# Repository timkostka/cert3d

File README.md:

# cert3d

Is your 3d printer firmware certified?

# What is Cert3D?

Cert3D is a project designed to certify the performance of 3d printer firmware.  It works by sending test g-code to the printer and monitoring the output of stepper motors.

## Why is Cert3D?

Within the 3d printer firmware community, there is a lack of verification of software features.  A massive amount of man-hours is spent on tracking down bugs which could otherwise be detected automatically.  The aim of this project is to enable developers to ensure features are working as intended before releasing software.

## Who benefits?

For developers, the testing framework helps identify bugs quickly allowing them to be fixed quickly.  The improved software quality due to this benefits.

## How does it work?

There are two parts to Cert3D--A hardware module and a software program.

### The hardware module

The hardware module is hooked up to the 3d printer board and monitors status of the stepper motors and other peripherals.

### The software program

The software sends runs a series of tests by sending g-code to the 3d printer board.  During these tests, it also reads back information from the hardware module.  It analyses these results to ensure the printer is working as intended.

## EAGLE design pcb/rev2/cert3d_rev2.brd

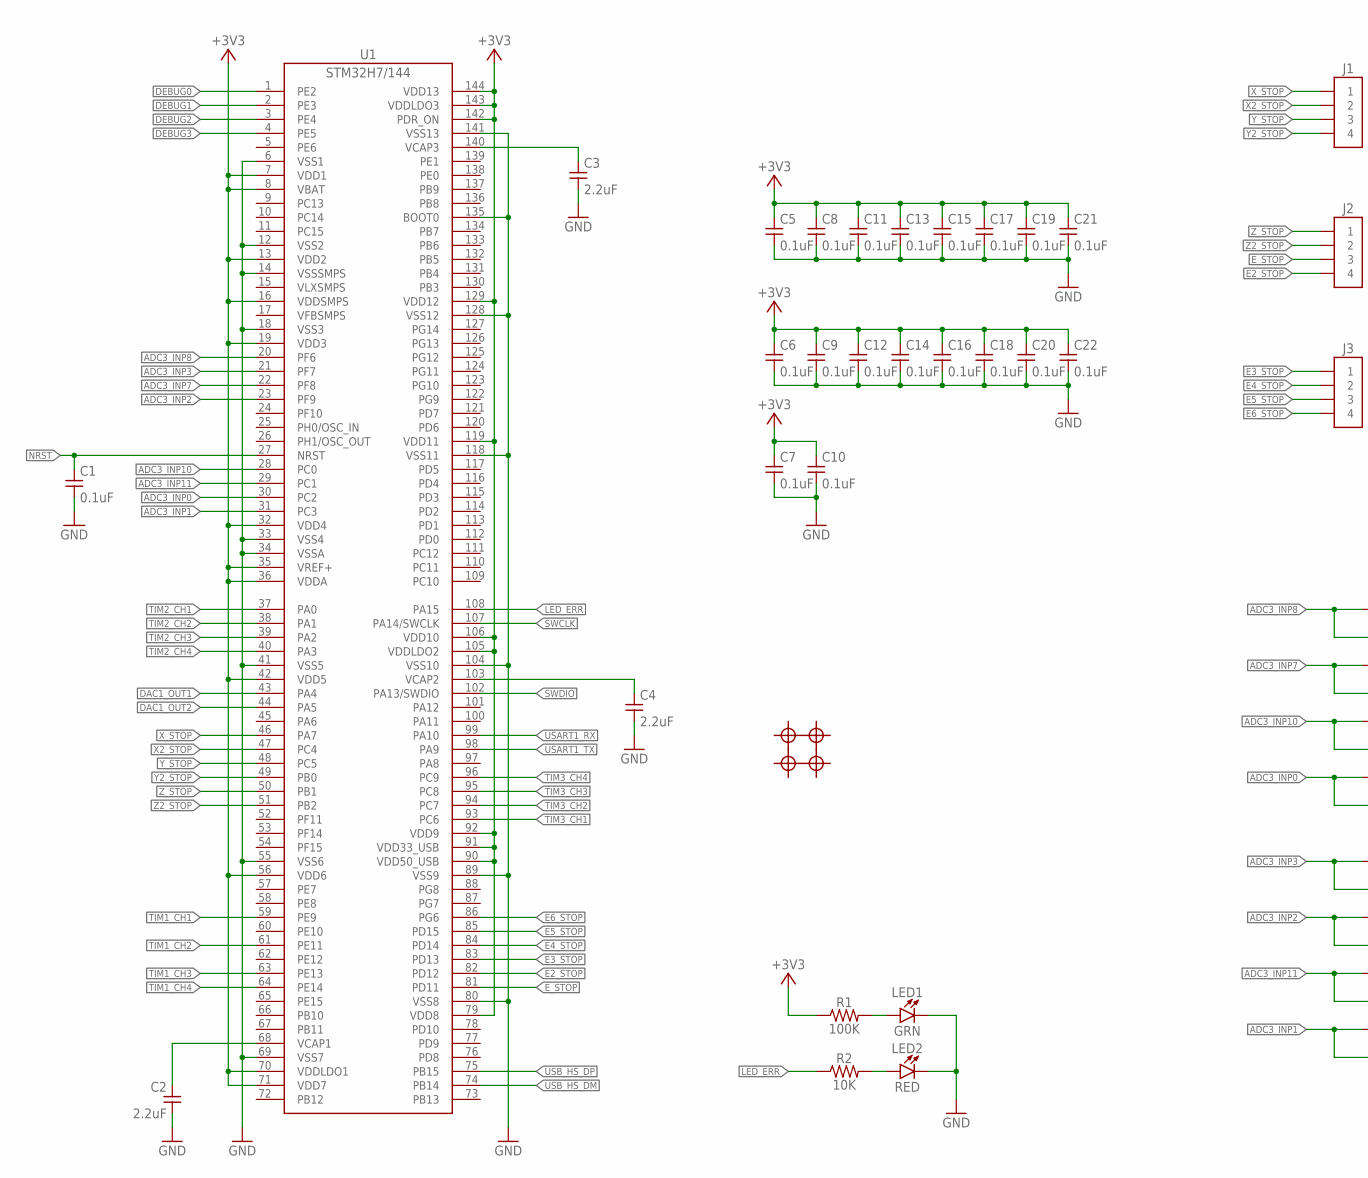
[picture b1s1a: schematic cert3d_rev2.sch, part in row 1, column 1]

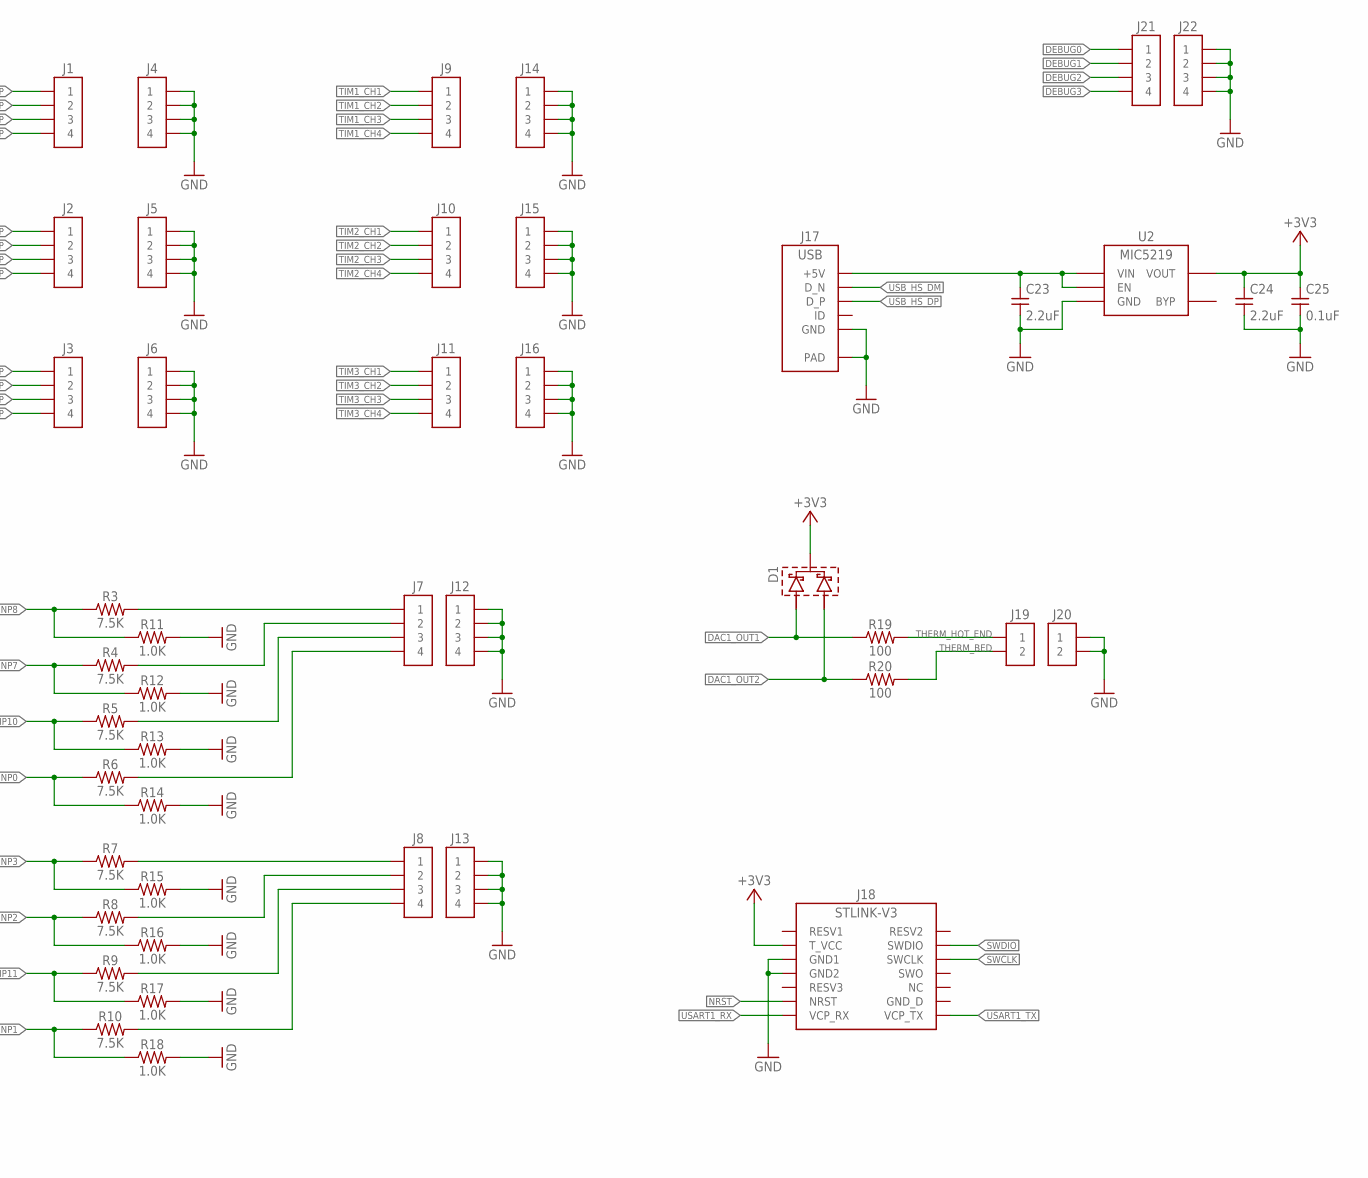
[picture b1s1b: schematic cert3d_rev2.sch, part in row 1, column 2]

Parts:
C1, C5, C6, C7, C8, C9, C10, C11, C12, C13, C14, C15, C16, C17, C18, C19, C20, C21, C22, C25: 0.1uF; C0805-5MIL
C2, C3, C4, C23, C24: 2.2uF; C0805-5MIL
D1: SCHOTTKY_DUAL_CCBAT54C; SOT23-3
FD1, FD2, FD3, FD4: FIDUCIAL; FID1MM
J1, J2, J3, J4, J5, J6, J7, J8, J9, J10, J11, J12, J13, J14, J15, J16, J21, J22: CONN4TSW-S; SAM-TSW-104-XX-X-S
J17: USB-5PINTOPVIA; HIR-ZX62R-B-5P-VIAS
J18: STLINK-V3/SWDCNC-3220; CNC-3220-14-0100-00
J19, J20: CONN2TSW-S; SAM-TSW-102-XX-X-S
LED1: GRN; CHIPLED0805-SMALL
LED2: RED; CHIPLED0805-SMALL
R1: 100K; RES0805R-5MIL
R2: 10K; RES0805R-5MIL
R3, R4, R5, R6, R7, R8, R9, R10: 7.5K; RES0805R-5MIL
R11, R12, R13, R14, R15, R16, R17, R18: 1.0K; RES0805R-5MIL
R19, R20: 100; RES0805R-5MIL
U1: STM32H745-144; LQFP144-20X20MM
U2: MIC5219; SOT23-5

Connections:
+3V3: C5.1, C6.1, C7.1, C8.1, C9.1, C10.1, C11.1, C12.1, C13.1, C14.1, C15.1, C16.1, C17.1, C18.1, C19.1, C20.1, C21.1, C22.1, C24.1, C25.1, D1.3 (C), J18.3 (T_VCC), R1.1, U1.7 (VDD1), U1.8 (VBAT), U1.13 (VDD2), U1.16 (VDDSMPS), U1.19 (VDD3), U1.32 (VDD4), U1.35 (VREF+), U1.36 (VDDA), U1.42 (VDD5), U1.56 (VDD6), U1.70 (VDDLDO1), U1.71 (VDD7), U1.79 (VDD8), U1.90 (VDD50_USB), U1.91 (VDD33_USB), U1.92 (VDD9), U1.105 (VDDLDO2), U1.106 (VDD10), U1.119 (VDD11), U1.129 (VDD12), U1.142 (PDR_ON), U1.143 (VDDLDO3), U1.144 (VDD13), U2.5 (VOUT)
ADC3_INP0: R6.1, R14.1, U1.30 (PC2)
ADC3_INP1: R10.1, R18.1, U1.31 (PC3)
ADC3_INP2: R8.1, R16.1, U1.23 (PF9)
ADC3_INP3: R7.1, R15.1, U1.21 (PF7)
ADC3_INP7: R4.1, R12.1, U1.22 (PF8)
ADC3_INP8: R3.1, R11.1, U1.20 (PF6)
ADC3_INP10: R5.1, R13.1, U1.28 (PC0)
ADC3_INP11: R9.1, R17.1, U1.29 (PC1)
DAC1_OUT1: D1.1 (A1), R19.1, U1.43 (PA4)
DAC1_OUT2: D1.2 (A2), R20.1, U1.44 (PA5)
DEBUG0: J21.1, U1.1 (PE2)
DEBUG1: J21.2, U1.2 (PE3)
DEBUG2: J21.3, U1.3 (PE4)
DEBUG3: J21.4, U1.4 (PE5)
E2_STOP: J2.4, U1.82 (PD12)
E3_STOP: J3.1, U1.83 (PD13)
E4_STOP: J3.2, U1.84 (PD14)
E5_STOP: J3.3, U1.85 (PD15)
E6_STOP: J3.4, U1.86 (PG6)
E_STOP: J2.3, U1.81 (PD11)
GND: C1.2, C2.2, C3.2, C4.2, C5.2, C6.2, C7.2, C8.2, C9.2, C10.2, C11.2, C12.2, C13.2, C14.2, C15.2, C16.2, C17.2, C18.2, C19.2, C20.2, C21.2, C22.2, C23.2, C24.2, C25.2, J4.1, J4.2, J4.3, J4.4, J5.1, J5.2, J5.3, J5.4, J6.1, J6.2, J6.3, J6.4, J12.1, J12.2, J12.3, J12.4, J13.1, J13.2, J13.3, J13.4, J14.1, J14.2, J14.3, J14.4, J15.1, J15.2, J15.3, J15.4, J16.1, J16.2, J16.3, J16.4, J17.5 (GND), J17.PAD@1 (PAD), J17.PAD@2 (PAD), J17.PAD@3 (PAD), J17.PAD@4 (PAD), J17.PAD@5 (PAD), J17.PAD@6 (PAD), J17.PAD@7 (PAD), J17.PAD@8 (PAD), J17.PAD@9 (PAD), J17.PAD@10 (PAD), J17.PAD@11 (PAD), J17.PAD@12 (PAD), J18.5 (GND1), J18.7 (GND2), J20.1, J20.2, J22.1, J22.2, J22.3, J22.4, LED1.C, LED2.C, R11.2, R12.2, R13.2, R14.2, R15.2, R16.2, R17.2, R18.2, U1.6 (VSS1), U1.12 (VSS2), U1.14 (VSSSMPS), U1.18 (VSS3), U1.33 (VSS4), U1.34 (VSSA), U1.41 (VSS5), U1.55 (VSS6), U1.69 (VSS7), U1.80 (VSS8), U1.89 (VSS9), U1.104 (VSS10), U1.118 (VSS11), U1.128 (VSS12), U1.135 (BOOT0), U1.141 (VSS13), U2.2 (GND)
LED_ERR: R2.1, U1.108 (PA15)
unnamed: C2.1, U1.68 (VCAP1)
unnamed: C4.1, U1.103 (VCAP2)
unnamed: J7.3, R5.2
unnamed: J7.1, R3.2
unnamed: J8.2, R8.2
unnamed: J7.2, R4.2
unnamed: C3.1, U1.140 (VCAP3)
unnamed: C23.1, J17.1 (+5V), U2.1 (VIN), U2.3 (EN)
unnamed: J8.3, R9.2
unnamed: J7.4, R6.2
unnamed: J8.4, R10.2
unnamed: J8.1, R7.2
unnamed: LED2.A, R2.2
unnamed: LED1.A, R1.2
NRST: C1.1, J18.11 (NRST), U1.27 (NRST)
SWCLK: J18.6 (SWCLK), U1.107 (PA14/SWCLK)
SWDIO: J18.4 (SWDIO), U1.102 (PA13/SWDIO)
THERM_BED: J19.2, R20.2
THERM_HOT_END: J19.1, R19.2
TIM1_CH1: J9.1, U1.59 (PE9)
TIM1_CH2: J9.2, U1.61 (PE11)
TIM1_CH3: J9.3, U1.63 (PE13)
TIM1_CH4: J9.4, U1.64 (PE14)
TIM2_CH1: J10.1, U1.37 (PA0)
TIM2_CH2: J10.2, U1.38 (PA1)
TIM2_CH3: J10.3, U1.39 (PA2)
TIM2_CH4: J10.4, U1.40 (PA3)
TIM3_CH1: J11.1, U1.93 (PC6)
TIM3_CH2: J11.2, U1.94 (PC7)
TIM3_CH3: J11.3, U1.95 (PC8)
TIM3_CH4: J11.4, U1.96 (PC9)
USART1_RX: J18.13 (VCP_RX), U1.99 (PA10)
USART1_TX: J18.14 (VCP_TX), U1.98 (PA9)
USB_HS_DM: J17.2 (D_N), U1.74 (PB14)
USB_HS_DP: J17.3 (D_P), U1.75 (PB15)
X2_STOP: J1.2, U1.47 (PC4)
X_STOP: J1.1, U1.46 (PA7)
Y2_STOP: J1.4, U1.49 (PB0)
Y_STOP: J1.3, U1.48 (PC5)
Z2_STOP: J2.2, U1.51 (PB2)
Z_STOP: J2.1, U1.50 (PB1)

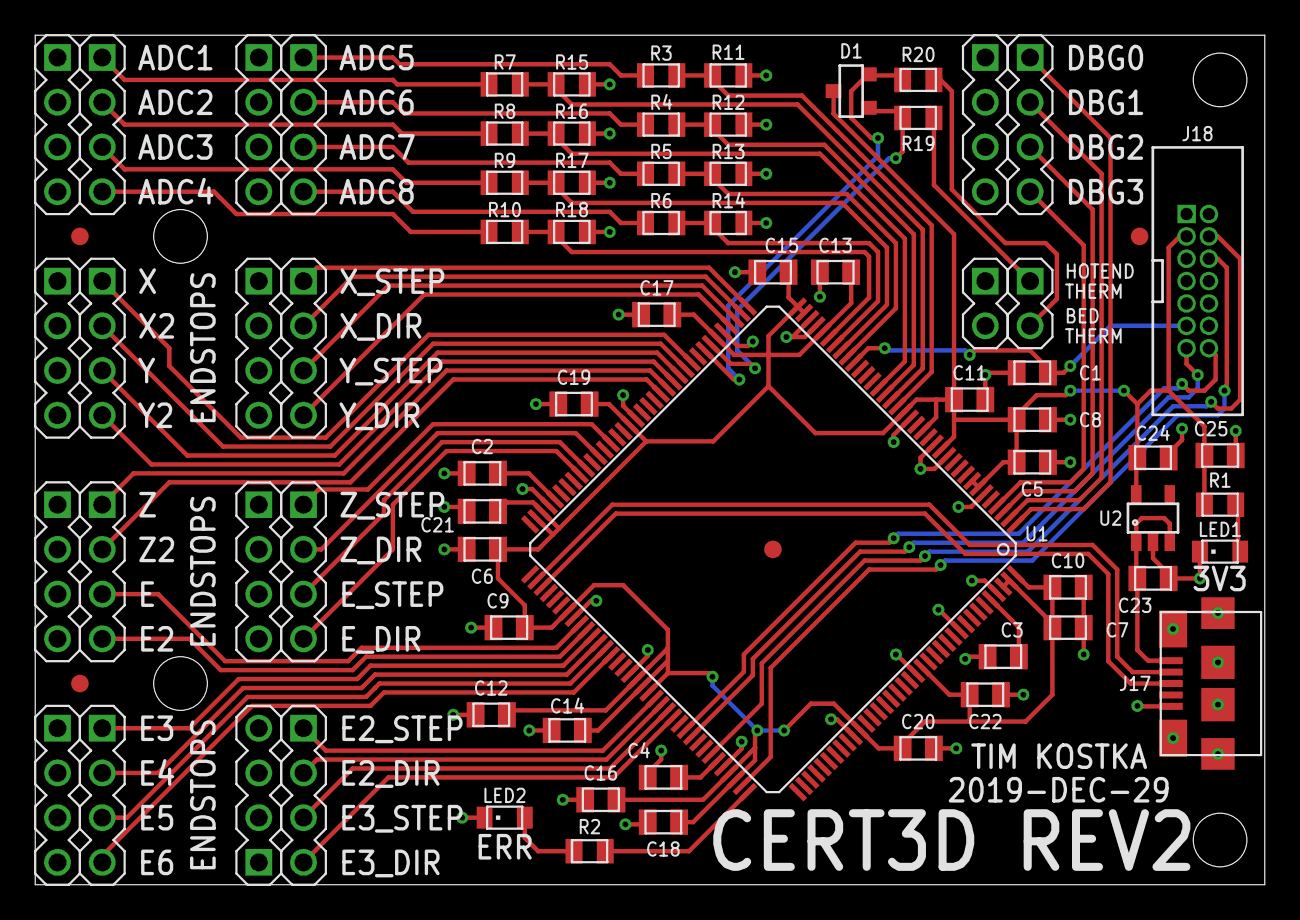
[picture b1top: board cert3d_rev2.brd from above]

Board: 2 copper layers, 69.8 x 48.3 mm, 76 parts (0 on the bottom side), 64 nets.

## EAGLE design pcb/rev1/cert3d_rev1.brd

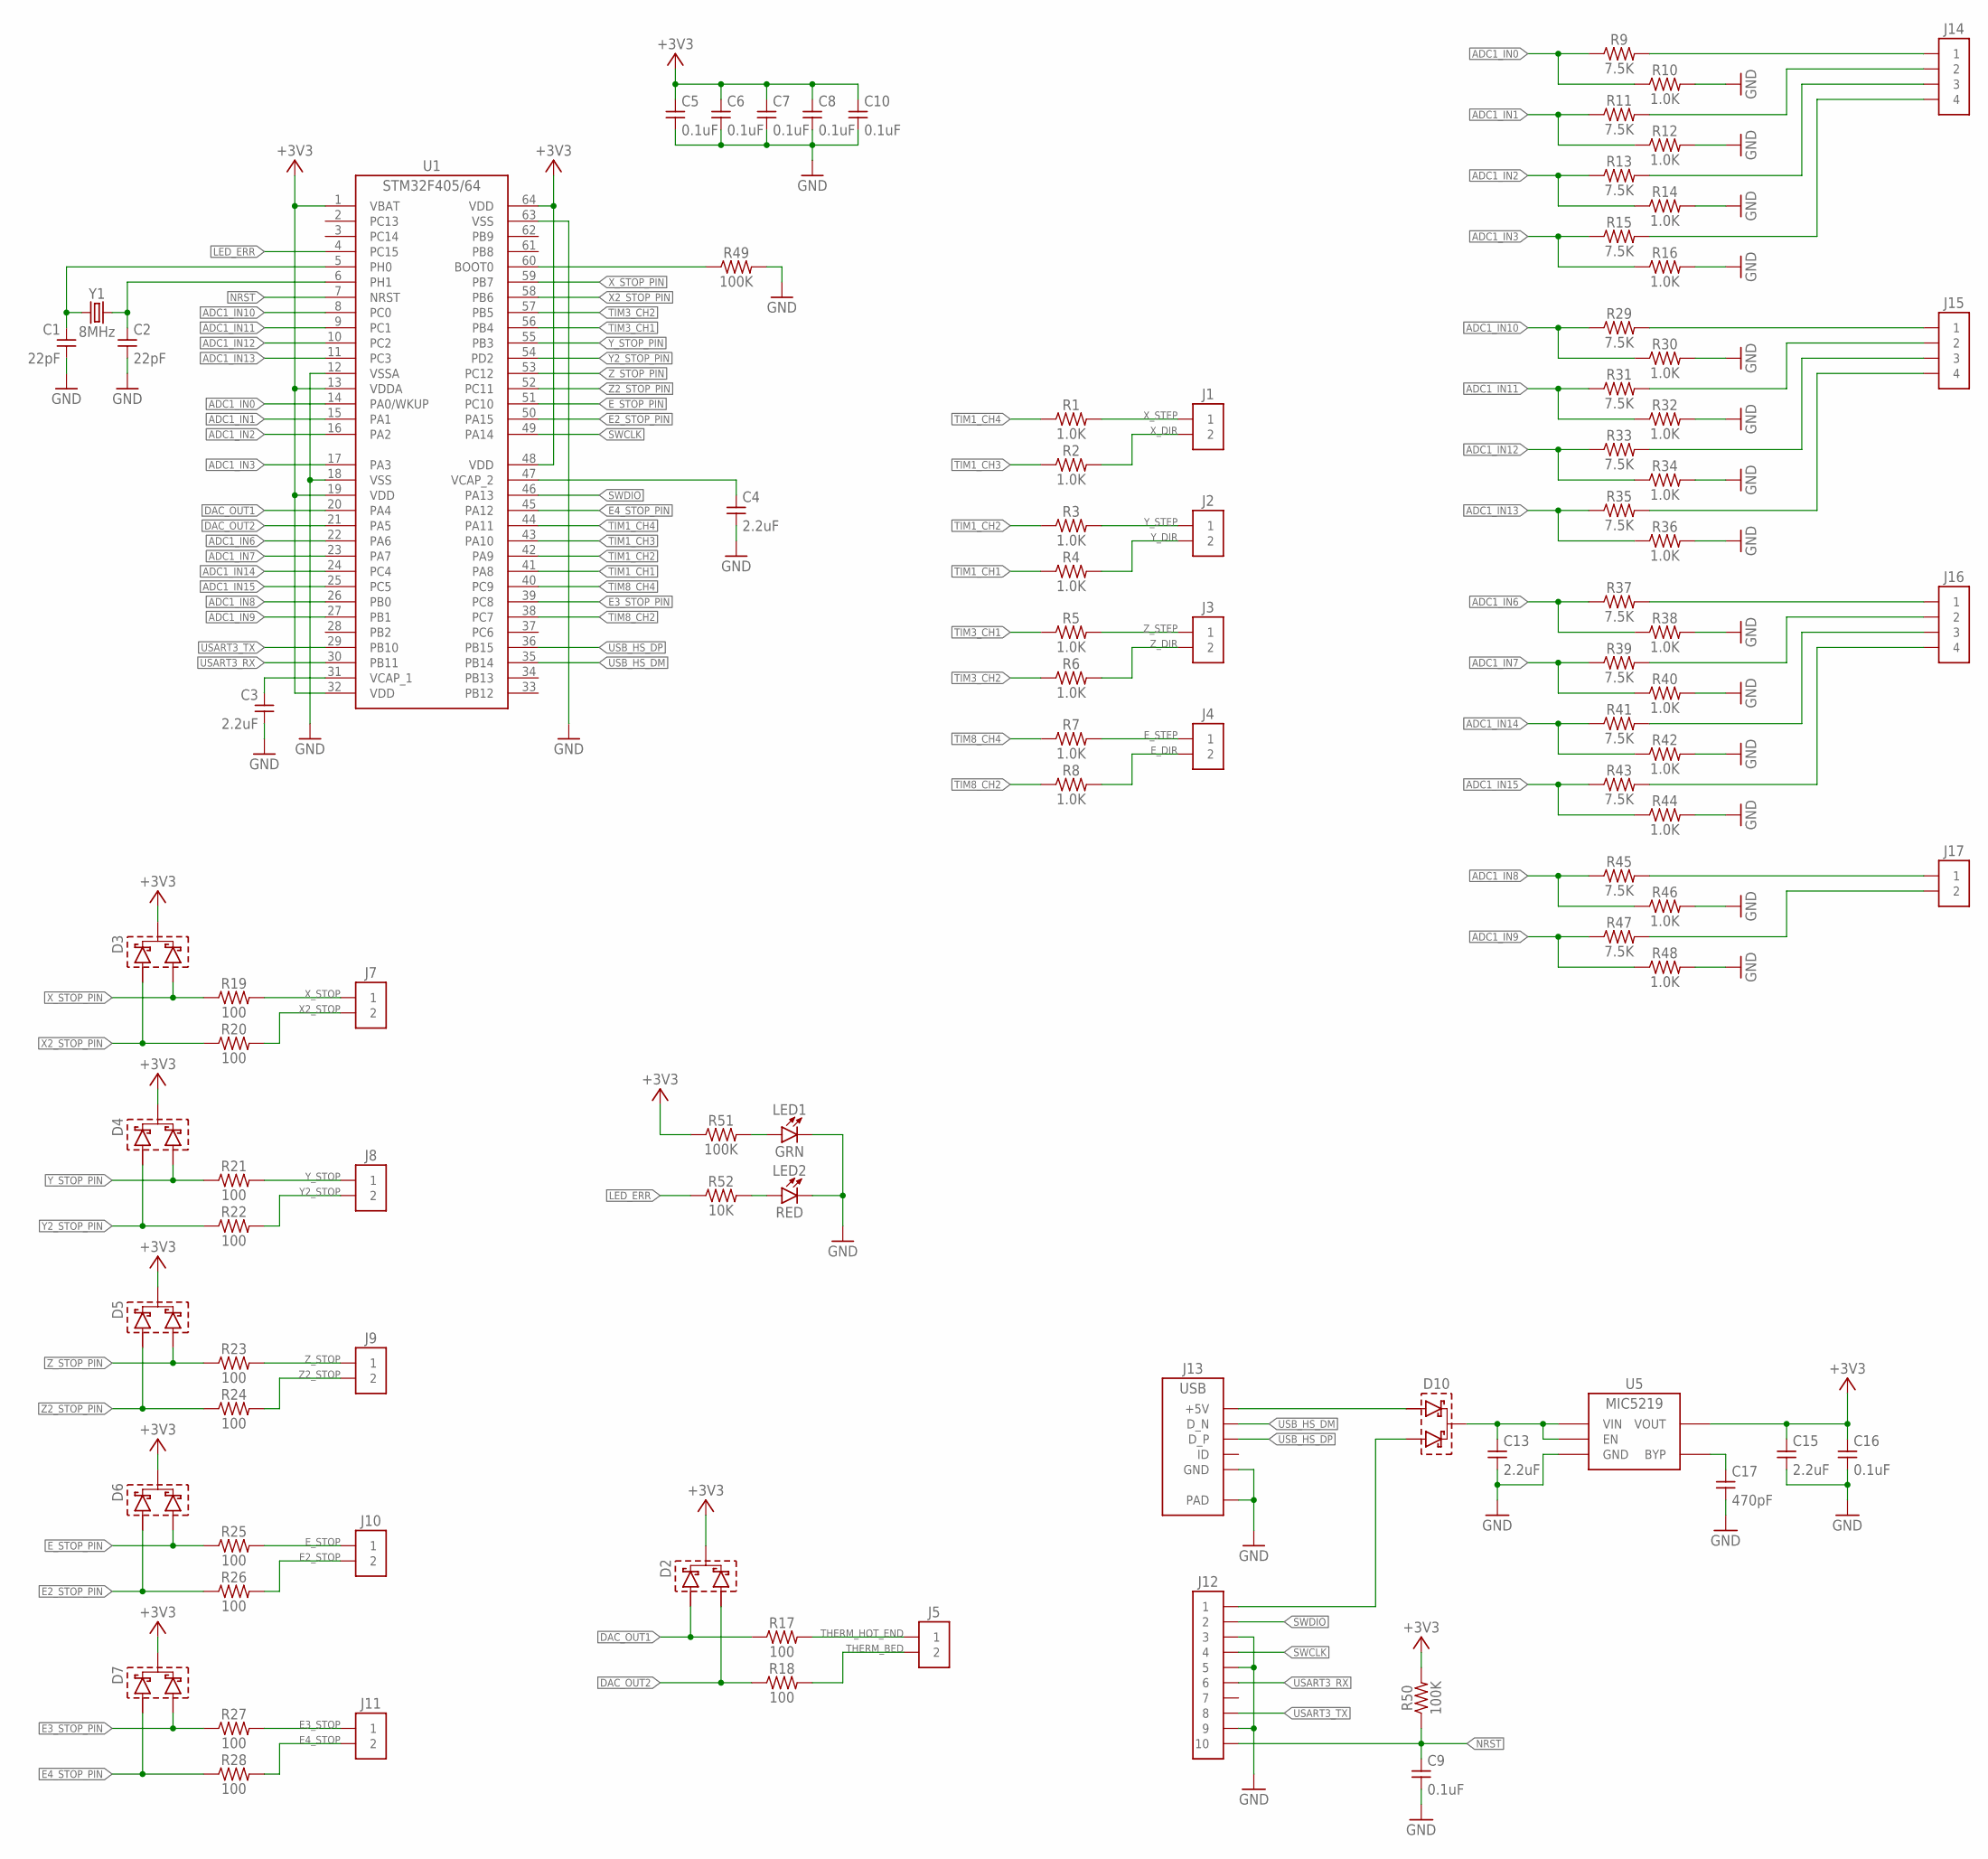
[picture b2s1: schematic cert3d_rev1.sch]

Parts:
C1, C2: 22pF; C0805-5MIL
C3, C4, C13, C15: 2.2uF; C0805-5MIL
C5, C6, C7, C8, C9, C10, C16: 0.1uF; C0805-5MIL
C17: 470pF; C0805-5MIL
D2, D3, D4, D5, D6, D7, D10: SCHOTTKY_DUAL_CCBAT54C; SOT23-3
J1, J2, J3, J4, J5, J7, J8, J9, J10, J11, J17: CONN2TSW-S; SAM-TSW-102-XX-X-S
J12: CONN10CNC-3220-10-0100-00; CNC-3220-10-0100-00
J13: USB-5PINTOPVIA; HIR-ZX62R-B-5P-VIAS
J14, J15, J16: CONN4TSW-S; SAM-TSW-104-XX-X-S
LED1: GRN; CHIPLED0805-SMALL
LED2: RED; CHIPLED0805-SMALL
R1, R2, R3, R4, R5, R6, R7, R8: 1.0K; RES0805R
R9, R11, R13, R15, R29, R31, R33, R35, R37, R39, R41, R43, R45, R47: 7.5K; RES0805R-5MIL
R10, R12, R14, R16, R30, R32, R34, R36, R38, R40, R42, R44, R46, R48: 1.0K; RES0805R-5MIL
R17, R18, R19, R20, R21, R22, R23, R24, R25, R26, R27, R28: 100; RES0805R-5MIL
R49, R50, R51: 100K; RES0805R-5MIL
R52: 10K; RES0805R-5MIL
U1: STM32F405/64; LQFP64-10X10MM
U5: MIC5219; SOT23-5
Y1: 8MHz; HC49US

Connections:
+3V3: C5.1, C6.1, C7.1, C8.1, C10.1, C15.1, C16.1, D2.3 (C), D3.3 (C), D4.3 (C), D5.3 (C), D6.3 (C), D7.3 (C), R50.2, R51.1, U1.1 (VBAT), U1.13 (VDDA), U1.19 (VDD), U1.32 (VDD), U1.48 (VDD), U1.64 (VDD), U5.5 (VOUT)
ADC1_IN0: R9.1, R10.1, U1.14 (PA0/WKUP)
ADC1_IN1: R11.1, R12.1, U1.15 (PA1)
ADC1_IN2: R13.1, R14.1, U1.16 (PA2)
ADC1_IN3: R15.1, R16.1, U1.17 (PA3)
ADC1_IN6: R37.1, R38.1, U1.22 (PA6)
ADC1_IN7: R39.1, R40.1, U1.23 (PA7)
ADC1_IN8: R45.1, R46.1, U1.26 (PB0)
ADC1_IN9: R47.1, R48.1, U1.27 (PB1)
ADC1_IN10: R29.1, R30.1, U1.8 (PC0)
ADC1_IN11: R31.1, R32.1, U1.9 (PC1)
ADC1_IN12: R33.1, R34.1, U1.10 (PC2)
ADC1_IN13: R35.1, R36.1, U1.11 (PC3)
ADC1_IN14: R41.1, R42.1, U1.24 (PC4)
ADC1_IN15: R43.1, R44.1, U1.25 (PC5)
DAC_OUT1: D2.1 (A1), R17.1, U1.20 (PA4)
DAC_OUT2: D2.2 (A2), R18.1, U1.21 (PA5)
E2_STOP: J10.2, R26.2
E2_STOP_PIN: D6.1 (A1), R26.1, U1.50 (PA15)
E3_STOP: J11.1, R27.2
E3_STOP_PIN: D7.2 (A2), R27.1, U1.39 (PC8)
E4_STOP: J11.2, R28.2
E4_STOP_PIN: D7.1 (A1), R28.1, U1.45 (PA12)
E_DIR: J4.2, R8.2
E_STEP: J4.1, R7.2
E_STOP: J10.1, R25.2
E_STOP_PIN: D6.2 (A2), R25.1, U1.51 (PC10)
GND: C1.2, C2.2, C3.2, C4.2, C5.2, C6.2, C7.2, C8.2, C9.2, C10.2, C13.2, C15.2, C16.2, C17.2, J12.3, J12.5, J12.9, J13.5 (GND), J13.PAD@1 (PAD), J13.PAD@2 (PAD), J13.PAD@3 (PAD), J13.PAD@4 (PAD), J13.PAD@5 (PAD), J13.PAD@6 (PAD), J13.PAD@7 (PAD), J13.PAD@8 (PAD), J13.PAD@9 (PAD), J13.PAD@10 (PAD), J13.PAD@11 (PAD), J13.PAD@12 (PAD), LED1.C, LED2.C, R10.2, R12.2, R14.2, R16.2, R30.2, R32.2, R34.2, R36.2, R38.2, R40.2, R42.2, R44.2, R46.2, R48.2, R49.2, U1.12 (VSSA), U1.18 (VSS), U1.63 (VSS), U5.2 (GND)
LED_ERR: R52.1, U1.4 (PC15)
unnamed: C2.1, U1.6 (PH1), Y1.2
unnamed: C1.1, U1.5 (PH0), Y1.1
unnamed: J14.2, R11.2
unnamed: C4.1, U1.47 (VCAP_2)
unnamed: J14.1, R9.2
unnamed: C3.1, U1.31 (VCAP_1)
unnamed: J14.3, R13.2
unnamed: J14.4, R15.2
unnamed: D10.2 (A2), J12.1
unnamed: C13.1, D10.3 (C), U5.1 (VIN), U5.3 (EN)
unnamed: J15.1, R29.2
unnamed: D10.1 (A1), J13.1 (+5V)
unnamed: J15.2, R31.2
unnamed: J15.3, R33.2
unnamed: J15.4, R35.2
unnamed: J16.1, R37.2
unnamed: J16.2, R39.2
unnamed: J16.3, R41.2
unnamed: J16.4, R43.2
unnamed: J17.1, R45.2
unnamed: J17.2, R47.2
unnamed: R49.1, U1.60 (BOOT0)
unnamed: LED2.A, R52.2
unnamed: LED1.A, R51.2
unnamed: C17.1, U5.4 (BYP)
NRST: C9.1, J12.10, R50.1, U1.7 (NRST)
SWCLK: J12.4, U1.49 (PA14)
SWDIO: J12.2, U1.46 (PA13)
THERM_BED: J5.2, R18.2
THERM_HOT_END: J5.1, R17.2
TIM1_CH1: R4.1, U1.41 (PA8)
TIM1_CH2: R3.1, U1.42 (PA9)
TIM1_CH3: R2.1, U1.43 (PA10)
TIM1_CH4: R1.1, U1.44 (PA11)
TIM3_CH1: R5.1, U1.56 (PB4)
TIM3_CH2: R6.1, U1.57 (PB5)
TIM8_CH2: R8.1, U1.38 (PC7)
TIM8_CH4: R7.1, U1.40 (PC9)
USART3_RX: J12.6, U1.30 (PB11)
USART3_TX: J12.8, U1.29 (PB10)
USB_HS_DM: J13.2 (D_N), U1.35 (PB14)
USB_HS_DP: J13.3 (D_P), U1.36 (PB15)
X2_STOP: J7.2, R20.2
X2_STOP_PIN: D3.1 (A1), R20.1, U1.58 (PB6)
X_DIR: J1.2, R2.2
X_STEP: J1.1, R1.2
X_STOP: J7.1, R19.2
X_STOP_PIN: D3.2 (A2), R19.1, U1.59 (PB7)
Y2_STOP: J8.2, R22.2
Y2_STOP_PIN: D4.1 (A1), R22.1, U1.54 (PD2)
Y_DIR: J2.2, R4.2
Y_STEP: J2.1, R3.2
Y_STOP: J8.1, R21.2
Y_STOP_PIN: D4.2 (A2), R21.1, U1.55 (PB3)
Z2_STOP: J9.2, R24.2
Z2_STOP_PIN: D5.1 (A1), R24.1, U1.52 (PC11)
Z_DIR: J3.2, R6.2
Z_STEP: J3.1, R5.2
Z_STOP: J9.1, R23.2
Z_STOP_PIN: D5.2 (A2), R23.1, U1.53 (PC12)

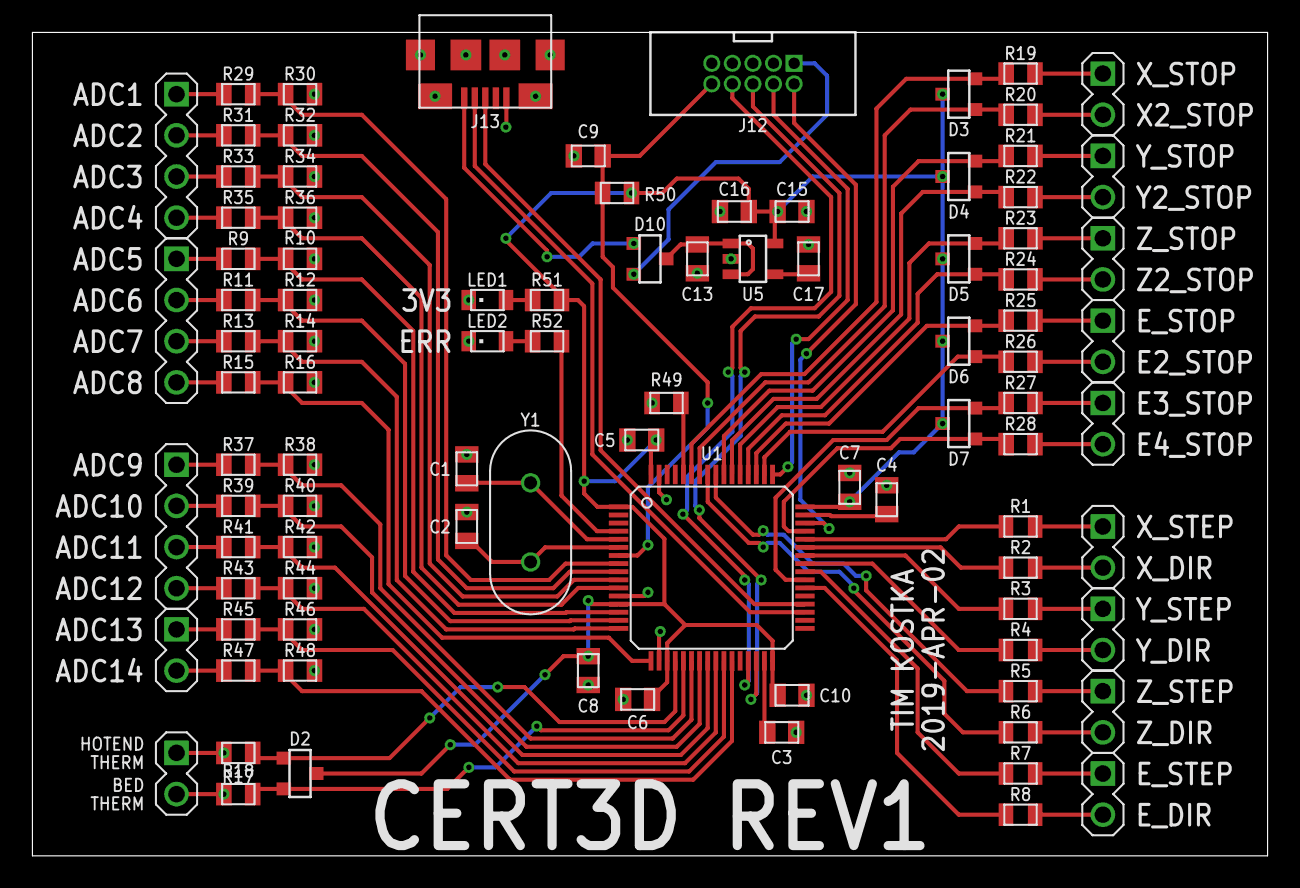
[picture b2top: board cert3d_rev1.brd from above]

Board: 2 copper layers, 76.2 x 50.8 mm, 94 parts (0 on the bottom side), 89 nets.

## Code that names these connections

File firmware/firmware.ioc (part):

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Mcu.Name=STM32F405RGTx
Mcu.Package=LQFP64
Mcu.UserName=STM32F405RGTx
PA0-WKUP.Signal=ADCx_IN0
PA1.Signal=ADCx_IN1
PA10.Signal=S_TIM1_CH3
PA11.Signal=S_TIM1_CH4
PA12.GPIOParameters=GPIO_Label
PA12.GPIO_Label=E4_STOP
PA12.Signal=GPIO_Output
PA13.Mode=Serial_Wire
PA13.Signal=SYS_JTMS-SWDIO
PA14.Mode=Serial_Wire
PA14.Signal=SYS_JTCK-SWCLK
PA15.GPIOParameters=GPIO_Label
PA15.GPIO_Label=E2_STOP
PA15.Signal=GPIO_Output
PA2.Signal=ADCx_IN2
PA3.Signal=ADCx_IN3
PA4.Signal=COMP_DAC1_group
PA5.Signal=COMP_DAC2_group
PA6.Signal=ADCx_IN6
PA7.Signal=ADCx_IN7
PA8.Signal=S_TIM1_CH1
PA9.Signal=S_TIM1_CH2
PB0.Signal=ADCx_IN8
PB1.Signal=ADCx_IN9
PB10.Mode=Asynchronous
PB10.Signal=USART3_TX
PB11.Mode=Asynchronous
PB11.Signal=USART3_RX
PB14.Mode=Device_Only_FS
PB14.Signal=USB_OTG_HS_DM
PB15.Mode=Device_Only_FS
PB15.Signal=USB_OTG_HS_DP
PB3.GPIOParameters=GPIO_Label
PB3.GPIO_Label=Y_STOP
PB3.Signal=GPIO_Output
PB4.Signal=S_TIM3_CH1
PB5.Signal=S_TIM3_CH2
PB6.GPIOParameters=GPIO_Label
PB6.GPIO_Label=X2_STOP
PB6.Signal=GPIO_Output
PB7.GPIOParameters=GPIO_Label
PB7.GPIO_Label=X_STOP
PB7.Signal=GPIO_Output
PC0.Signal=ADCx_IN10
PC1.Signal=ADCx_IN11
PC10.GPIOParameters=GPIO_Label
PC10.GPIO_Label=E_STOP
PC10.Signal=GPIO_Output
PC11.GPIOParameters=GPIO_Label
PC11.GPIO_Label=Z2_STOP
PC11.Signal=GPIO_Output
PC12.GPIOParameters=GPIO_Label
PC12.GPIO_Label=Z_STOP
PC12.Signal=GPIO_Output
PC15-OSC32_OUT.GPIOParameters=GPIO_Label
PC15-OSC32_OUT.GPIO_Label=LED_ERR
PC15-OSC32_OUT.Signal=GPIO_Output
PC2.Signal=ADCx_IN12
PC3.Signal=ADCx_IN13
PC4.Signal=ADCx_IN14
PC5.Signal=ADCx_IN15
PC7.Signal=S_TIM8_CH2
PC8.GPIOParameters=GPIO_Label
PC8.GPIO_Label=E3_STOP
PC8.Signal=GPIO_Output
PC9.Signal=S_TIM8_CH4
PD2.GPIOParameters=GPIO_Label
PD2.GPIO_Label=Y2_STOP
PD2.Signal=GPIO_Output
PH0-OSC_IN.Mode=HSE-External-Oscillator
PH0-OSC_IN.Signal=RCC_OSC_IN
PH1-OSC_OUT.Mode=HSE-External-Oscillator
PH1-OSC_OUT.Signal=RCC_OSC_OUT
RCC.HSE_VALUE=8000000
RCC.SYSCLKFreq_VALUE=168000000
RCC.SYSCLKSource=RCC_SYSCLKSOURCE_PLLCLK
board=custom

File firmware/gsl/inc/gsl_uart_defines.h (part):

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#endif

// tx pin
// USART1 TX can be PA9 or PB6
#ifndef GSL_USART1_PIN_TX
#define GSL_USART1_PIN_TX kPinA9
#endif

// rx pin
// USART1 RX can be PA10 or PB7
#ifndef GSL_USART1_PIN_RX
#define GSL_USART1_PIN_RX kPinA10
#endif
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#endif

// tx pin
// USART2 TX can be PA2, PD5
#ifndef GSL_USART2_PIN_TX
#define GSL_USART2_PIN_TX kPinA2
#endif

// rx pin
// USART2 RX can be PA3, PD6
#ifndef GSL_USART2_PIN_RX
#define GSL_USART2_PIN_RX kPinA3
#endif
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#endif

// tx pin
// USART3 TX can be PB10, PC10, PD8
#ifndef GSL_USART3_PIN_TX
#define GSL_USART3_PIN_TX kPinB10
#endif

// rx pin
// USART3 TX can be PB11, PC11, PD9
#ifndef GSL_USART3_PIN_RX
#define GSL_USART3_PIN_RX kPinB11
#endif
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#endif

// tx pin
// UART4 TX can be PA0, PC10
#ifndef GSL_UART4_PIN_TX
#define GSL_UART4_PIN_TX kPinA0
#endif

// rx pin
// UART4 RX can be PA1, PC11
#ifndef GSL_UART4_PIN_RX
#define GSL_UART4_PIN_RX kPinA1
#endif
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#endif

// tx pin
// UART5 TX can be PC12
#define GSL_UART5_PIN_TX kPinC12

// rx pin
// UART5 TX can be PD2
#define GSL_UART5_PIN_RX kPinD2

// initialization routine
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#endif

// tx pin
// USART6 TX can be PC6, PG14
#ifndef GSL_USART6_PIN_TX
#define GSL_USART6_PIN_TX kPinC6
#endif

// rx pin
// USART6 RX can be PC7, PG9
#ifndef GSL_USART6_PIN_RX
#define GSL_USART6_PIN_RX kPinC7
#endif
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#endif

// tx pin
// UART7 TX can be PE8, PF7
#ifndef GSL_UART7_PIN_TX
#define GSL_UART7_PIN_TX kPinE8
#endif

// rx pin
// UART7 RX can be PE7, PF6
#ifndef GSL_UART7_PIN_RX
#define GSL_UART7_PIN_RX kPinE7
#endif
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
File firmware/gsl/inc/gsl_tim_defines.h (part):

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// *** TIM1 ***
// ************

// TIM1_CH1 pin
#ifndef GSL_TIM1_PIN_CH1
#define GSL_TIM1_PIN_CH1 kPinA8
#endif

// TIM1_CH2 pin
#ifndef GSL_TIM1_PIN_CH2
#define GSL_TIM1_PIN_CH2 kPinA9
#endif

// TIM1_CH3 pin
#ifndef GSL_TIM1_PIN_CH3
#define GSL_TIM1_PIN_CH3 kPinA10
#endif

// TIM1_CH4 pin
#ifndef GSL_TIM1_PIN_CH4
#define GSL_TIM1_PIN_CH4 kPinA11
#endif
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// *** TIM2 ***
// ************

// TIM2_CH1 pin
#ifndef GSL_TIM2_PIN_CH1
#define GSL_TIM2_PIN_CH1 kPinA0
#endif

// TIM2_CH2 pin
#ifndef GSL_TIM2_PIN_CH2
#define GSL_TIM2_PIN_CH2 kPinA1
#endif

// TIM2_CH3 pin
#ifndef GSL_TIM2_PIN_CH3
#define GSL_TIM2_PIN_CH3 kPinA2
#endif

// TIM2_CH4 pin
#ifndef GSL_TIM2_PIN_CH4
#define GSL_TIM2_PIN_CH4 kPinA3
#endif
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// *** TIM3 ***
// ************

// TIM3_CH1 pin
#ifndef GSL_TIM3_PIN_CH1
#define GSL_TIM3_PIN_CH1 kPinA6
#endif

// TIM3_CH2 pin
#ifndef GSL_TIM3_PIN_CH2
#define GSL_TIM3_PIN_CH2 kPinA7
#endif

// TIM3_CH3 pin
#ifndef GSL_TIM3_PIN_CH3
#define GSL_TIM3_PIN_CH3 kPinB0
#endif

// TIM3_CH4 pin
#ifndef GSL_TIM3_PIN_CH4
#define GSL_TIM3_PIN_CH4 kPinB1
#endif
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#define GSL_TIM8_PIN_CH1 kPinC6
#endif

// TIM8_CH2 pin
#ifndef GSL_TIM8_PIN_CH2
#define GSL_TIM8_PIN_CH2 kPinC7
#endif
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#define GSL_TIM8_PIN_CH3 kPinC8
#endif

// TIM8_CH4 pin
#ifndef GSL_TIM8_PIN_CH4
#define GSL_TIM8_PIN_CH4 kPinC9
#endif
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
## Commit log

2019-03-29 added .gitignore
2019-03-29 added beginnings of GUI results view
2019-03-29 allow zooming/panning of data with mouse
2019-03-29 added selecting edges with mouse to measure the time between
2019-03-29 add timestamp to selected time range
2019-03-29 erase snaptime range if end isn't found. don't allow same start and end point
2019-03-29 add wxFormBuilder project file
2019-03-30 minor updates to time delta selection
2019-03-30 added hardware plans for simulating printer peripheral
2019-03-31 Added DMA stream assignments
2019-03-31 Expanded hardware planning
2019-03-31 changed (corrected) typical thermistor value is 100K
2019-04-01 added software.md
2019-04-03 added EaglePCB ignores to .gitignore
2019-04-03 added EaglePCB project directory
2019-04-03 added renders of rev1 board
2019-04-03 ignore Eagle CAM output files
2019-04-03 added 2000dpi board renders
2019-04-03 added some .idea files to .gitignore
2019-04-03 added .idea files
2019-04-03 formatted files with Black
2019-04-04 beginning rewrite of software for modular channels
2019-04-04 improved right-click drag panning behavior
2019-04-04 implemented drag/drop to rearrange channels
2019-04-04 moved drawing of a BilevelData into its own function added PlotData class
2019-04-04 added drawing of PlotData type channel
2019-04-04 performance improvements on drawing BilevelData
2019-04-05 Implemented multiple signals per channel.
2019-04-05 adjusted form elements
2019-04-09 updated eagle board files with part numbers
2019-04-09 updated hardware plan
2019-04-09 added EXE creation script
2019-04-09 clean up code
2019-04-09 added snaptime functionality back in
2019-04-09 improved snaptime drawing alignment
2019-04-09 improved alignment of bilevel data for thick lines
2019-04-10 added auto-selection of dt for vertical bars for quick time reference
2019-04-10 improved snaptime display
2019-04-10 implemented submenu to change signal color/thickness
2019-04-10 reworked BilevelData to be efficient for super large data sets
2019-04-10 display stipple pattern when bilevel data sets are zoomed way out.
2019-04-10 clip stipple region to data region
2019-04-10 formatting, commented some debug print statements
2019-04-11 minor edits
2019-04-11 moved dpi functions into a dpi.py file made ScopePanel padding/thicknesses adjusted for dpi
2019-04-18 added icon files
2019-04-18 many updates
2019-04-18 removed unused code
2019-04-18 major updates refactoring files and objects
2019-04-18 got drawing a BilevelData working again.
2019-04-18 added draw routine to TriStateData
2019-04-18 improvements to zoom with mouse wheel
2019-04-18 implemented zooming to simplified representations
2019-04-18 improved simplified representation generation
2019-04-19 several updates
2019-04-19 moved child thread functionality into separate class
2019-04-19 deleted unused code improved header information, interpretation and validity checking
2019-04-21 discard data by default instead of not reading it to prevent old data from remaining in the buffer.
2019-04-21 implemented PlotData to work with the new structure
2019-04-21 added postprocessing of signals to get pos/vel/acc
2019-04-21 added file_open to open binary files
2019-04-21 added trimming signals functionality
2019-04-22 improved postprocessing of POS/VEL/ACC signals.
2019-04-22 improved signal trimming
2019-04-22 improved test window layout
2019-04-23 big update to add testing framework and control of printer port
2019-04-23 implemented vertical scroll bar on scope_panel
2019-04-24 update to test runner to be able to save/load/modify tests
2019-04-24 added test creator for g-code arc
2019-04-24 added thoughts on simulating hotend position
2019-04-24 added calculation of in-plane XY_VEL delete E_POS from results move E_VEL to its own scope channel delete *.ACC from results (for now)
2019-04-24 close children if main frame is exited before children
2019-04-25 added FuzzyPlotData for reducing PlotData and related functionality
2019-04-26 added items in signal context menu to view master data at any zoom level
2019-04-28 added option to clear buffer added option to flush log file immediately create INI directories silently
2019-04-28 updated .gitignore to ignore some auto-generated files
2019-04-28 added C3D board firmware
2019-04-28 move C3D and printer status to status bar
2019-04-29 implemented ADC handling
2019-04-29 made LOGxxx macros require semicolon afterwards
2019-04-29 reworked some ASSERT_* macros to avoid warning messages
2019-04-29 changed foreground color to black for some text-elements
2019-04-30 reworked drawing of FuzzyPlotData implemented FuzzyPlotData.get_reduced_data small code cleanup
2019-04-30 minor code updates
2019-04-30 added endstop emulation
2019-05-02 updated .gitignore to ignore run configurations
2019-05-08 misc updates
2019-05-08 added thoughts for rev2 hardware
2019-10-18 updates for new header/data packet versions
2019-10-18 add DMA monitor
2019-10-22 final updates to get things working
2019-10-22 updates to get ADC channels working
2019-10-22 capture signals on both edges
2019-12-29 added rev2 PCB
2019-12-30 added doc on solving equations of motion
2019-12-30 added equation of motion spreadsheet
2019-12-30 apply Python Black on save
2019-12-30 added equations of motion solver example
2019-12-30 updates on solving equations of motion
2019-12-31 updated derivation on equation of motion
2019-12-31 added dual simulation method
2019-12-31 renamed files
2020-01-01 finalized rev2 PWB
2020-01-01 more notes on solving equations of motion
2020-01-05 added s curve motion
2020-01-06 work on motion planner script
2020-01-08 work on motion planner
